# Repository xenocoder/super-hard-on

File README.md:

ZVex Super Hard On for 1590a

Version 1.0 - 11/12/2013
First finished version
Uploaded to OSHPark for order

Version 1.1 11/23/2013
Changed wire widths to 0.024
Replaced all components from G-M to madbean due to really small pads and drill sizes. This increased drill sizes on parts from 0.7mm to 1mm. Also changed pad size from auto to 1.89mm.
Uploaded to OSHPark. Will test board for verification before ordering

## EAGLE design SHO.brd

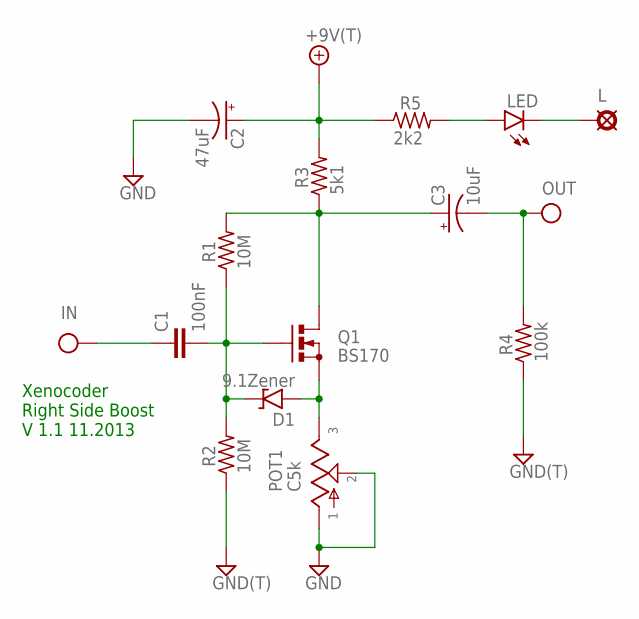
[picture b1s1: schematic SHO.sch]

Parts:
+9V: +9V(T); SQUARE
C1: 100nF; 075X030
C2: 47uF; 063_025
C3: 10uF; 063_025
D1: 9.1Zener; DO35-3
G: GND(T); SQUARE
GND: GND(T); SQUARE
IN: IN(T); SQUARE
L: 3mm; SQUARE
LED: LED3MM
OUT: OUT(T); SQUARE
POT1: C5k; 16MM_PCB_PADS
Q1: BS170; SOT54ES
R1, R2: 10M; R0207/3
R3: 5k1; R0207/3
R4: 100k; R0207/3
R5: 2k2; R0207/3

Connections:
+9V: +9V.1, C2.+, R3.2, R5.1
GND: C2.-, G.1, GND.1, POT1.1, POT1.2, R2.1, R4.1
IN: C1.1, IN.1
unnamed: C3.+, Q1.D, R1.2, R3.1
unnamed: D1.A, POT1.3, Q1.S
unnamed: C1.2, D1.C, Q1.G, R1.1, R2.2
unnamed: LED.A, R5.2
unnamed: L.1, LED.K (C)
OUT: C3.-, OUT.1, R4.2

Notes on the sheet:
Xenocoder Right Side Boost V 1.1 11.2013

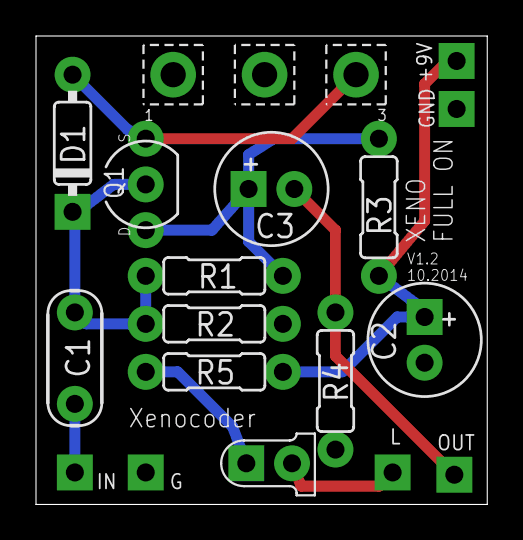
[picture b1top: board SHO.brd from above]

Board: 2 copper layers, 25.1 x 26.0 mm, 18 parts (0 on the bottom side), 9 nets.

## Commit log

2015-10-08 New schematic and Board layout
2015-10-08 Updated layout
